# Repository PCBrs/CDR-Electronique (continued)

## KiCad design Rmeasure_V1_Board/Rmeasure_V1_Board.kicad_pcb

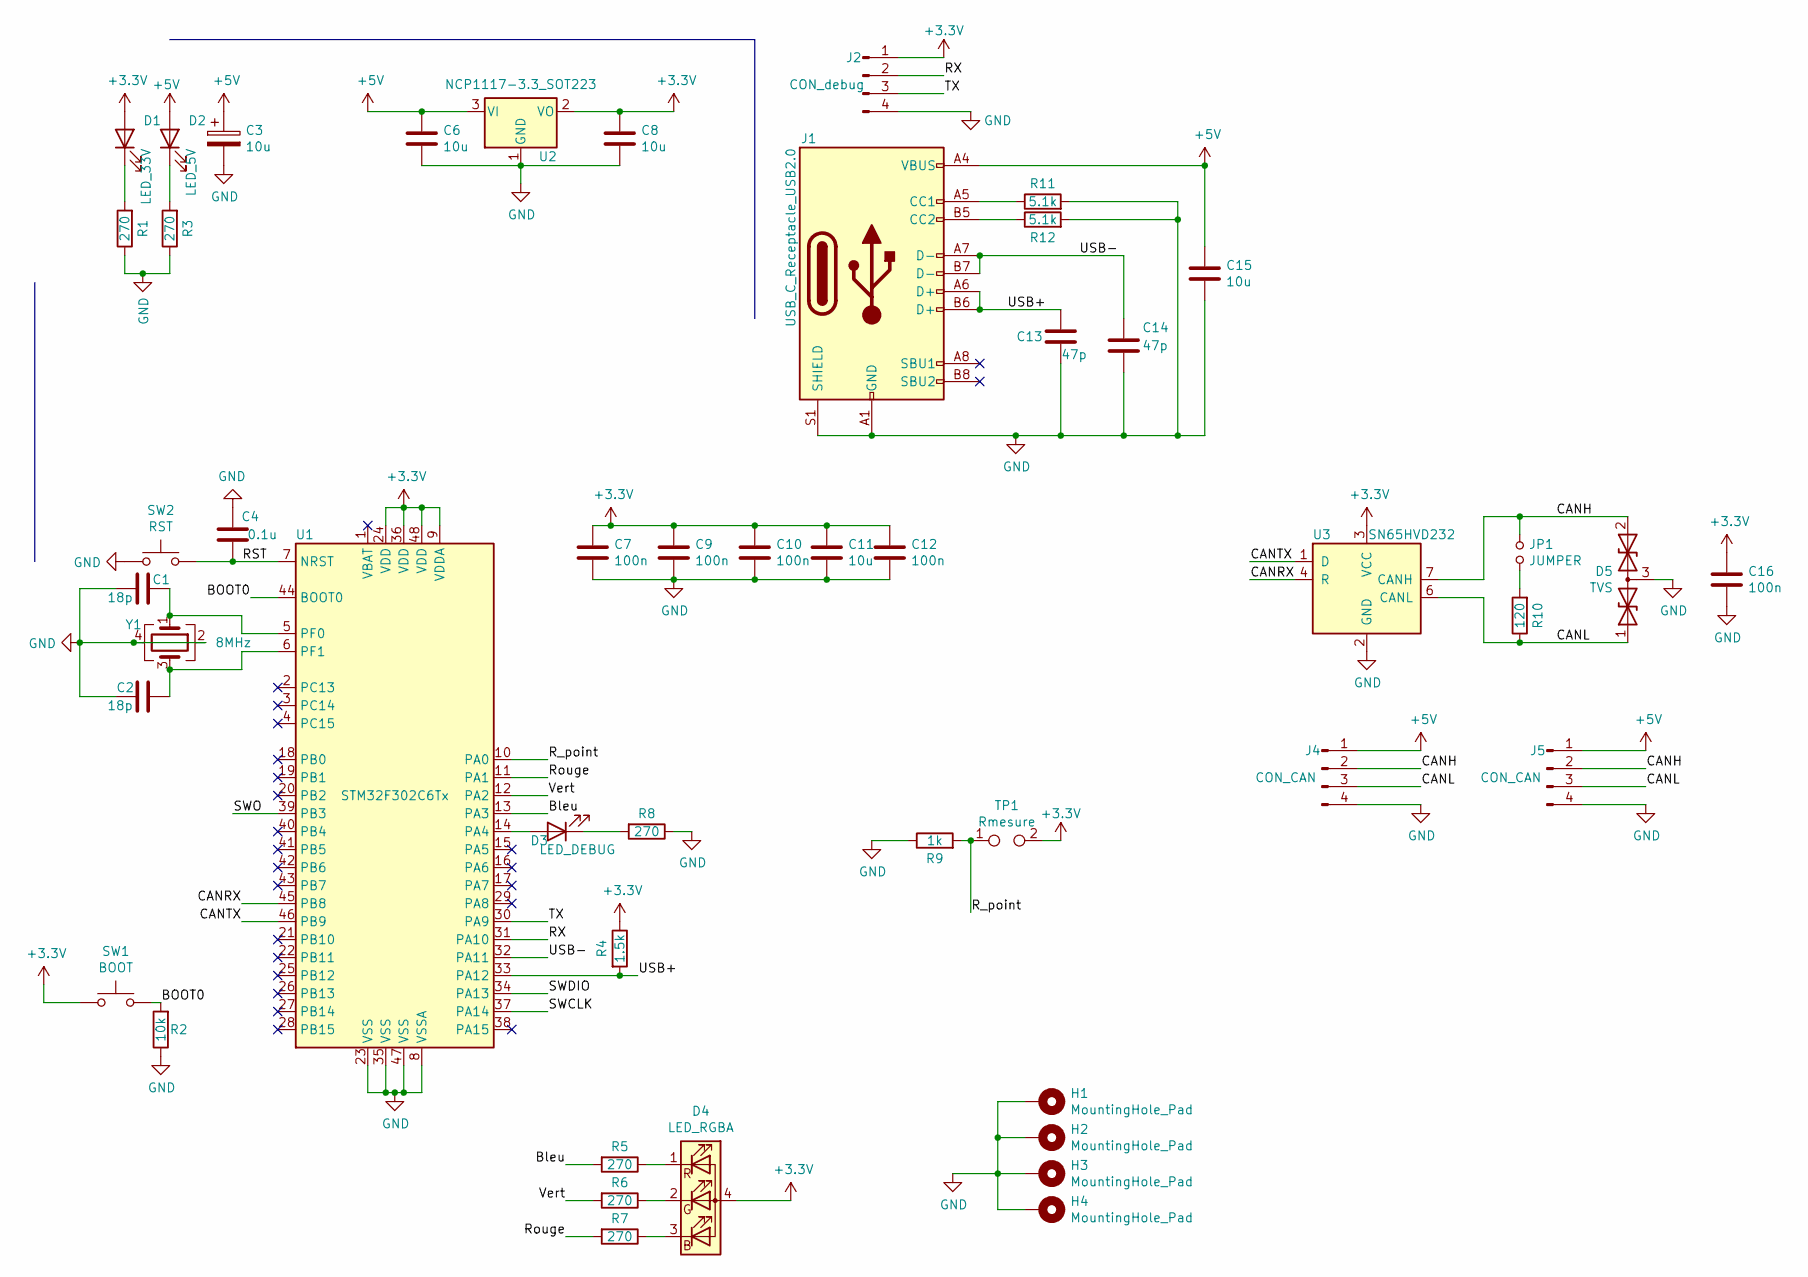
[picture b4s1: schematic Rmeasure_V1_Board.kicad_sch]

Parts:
C1, C2: 18p; C_0805_2012Metric_Pad1.18x1.45mm_HandSolder
C3: 10u; CP_Radial_D4.0mm_P2.00mm
C4: 0.1u; C_0805_2012Metric
C6, C8, C11, C15: 10u; C_0805_2012Metric
C7, C9, C10, C12, C16: 100n; C_0805_2012Metric
C13, C14: 47p; C_0805_2012Metric
D1: LED_33V; LED_0805_2012Metric
D2: LED_5V; LED_0805_2012Metric
D3: LED_DEBUG; LED_0805_2012Metric
D4: LED_RGBA; LED_SK6812_EC15_1.5x1.5mm
D5: TVS; SOT-23
H1, H2, H3, H4: MountingHole_Pad; MountingHole_3.2mm_M3_Pad_Via
J1: USB_C_Receptacle_USB2.0; USB_C_Receptacle_GCT_USB4085
J2: CON_debug; Wuerth_2.54mm_4pins_61900411121
J4, J5: CON_CAN; 690367290476
JP1: JUMPER; PinHeader_1x02_P2.54mm_Vertical
R1, R3, R5, R6, R7, R8: 270; R_0805_2012Metric
R2: 10k; R_0805_2012Metric
R4: 1.5k; R_0805_2012Metric
R9: 1k; R_0805_2012Metric
R10: 120; R_0805_2012Metric
R11, R12: 5.1k; R_0805_2012Metric
SW1: BOOT; SW_SPST_CK_RS282G05A3
SW2: RST; SW_SPST_CK_RS282G05A3
TP1: Rmesure; TestPoint_Pad_4.0x4.0mm
U1: STM32F302C6Tx; LQFP-48_7x7mm_P0.5mm
U2: NCP1117-3.3_SOT223; SOT-223-3_TabPin2
U3: SN65HVD232; SOIC-8_3.9x4.9mm_P1.27mm
Y1: 8MHz; Crystal_SMD_5032-4Pin_5.0x3.2mm

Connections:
+3V3: C7.1, C8.1, C9.1, C10.1, C11.1, C12.1, C16.1, D1.2 (A), D4.4 (A), J2.1, R4.1, SW1.1, TP1.2, U1.9 (VDDA), U1.24 (VDD), U1.36 (VDD), U1.48 (VDD), U2.2 (VO), U3.3 (VCC); also elsewhere on the board
+5V: C3.1, C6.1, C15.1, D2.2 (A), J1.A4 (VBUS), J1.A9 (VBUS), J1.B4 (VBUS), J1.B9 (VBUS), J4.1, J5.1, U2.3 (VI)
/BOOT0: R2.2, SW1.2, U1.44 (BOOT0); also elsewhere on the board
/Bleu: R5.2, U1.13 (PA3)
/CANH: D5.2 (A2), J4.2, J5.2, JP1.1, U3.7 (CANH)
/CANL: D5.1 (A1), J4.3, J5.3, R10.1, U3.6 (CANL)
/CANRX: U1.45 (PB8), U3.4 (R)
/CANTX: U1.46 (PB9), U3.1 (D)
/RST: C4.1, SW2.2, U1.7 (NRST); also elsewhere on the board
/RX: J2.2, U1.31 (PA10)
/R_point: R9.2, TP1.1, U1.10 (PA0)
/Rouge: R7.2, U1.11 (PA1)
/SWCLK: U1.37 (PA14)
/SWDIO: U1.34 (PA13)
/SWO: U1.39 (PB3)
/TX: J2.3, U1.30 (PA9)
/USB+: C13.1, J1.A6 (D+), J1.B6 (D+), R4.2, U1.33 (PA12)
/USB-: C14.1, J1.A7 (D-), J1.B7 (D-), U1.32 (PA11)
/Vert: R6.2, U1.12 (PA2)
GND: C1.2, C2.2, C3.2, C4.2, C6.2, C7.2, C8.2, C9.2, C10.2, C11.2, C12.2, C13.2, C14.2, C15.2, C16.2, D5.3 (common), H1.1, H2.1, H3.1, H4.1, J1.A1 (GND), J1.A12 (GND), J1.B1 (GND), J1.B12 (GND), J1.S1 (SHIELD), J2.4, J4.4, J5.4, R1.1, R2.1, R3.1, R8.1, R9.1, R11.2, R12.2, SW2.1, U1.8 (VSSA), U1.23 (VSS), U1.35 (VSS), U1.47 (VSS), U2.1 (GND), U3.2 (GND), Y1.2, Y1.4; also elsewhere on the board
unnamed: C1.1, U1.5 (PF0), Y1.1
unnamed: C2.1, U1.6 (PF1), Y1.3
unnamed: D1.1 (K), R1.2
unnamed: D2.1 (K), R3.2
unnamed: D3.1 (K), R8.2
unnamed: D3.2 (A), U1.14 (PA4)
unnamed: D4.1 (RK), R5.1
unnamed: D4.2 (GK), R6.1
unnamed: D4.3 (BK), R7.1
unnamed: J1.A5 (CC1), R11.1
unnamed: J1.B5 (CC2), R12.1
unnamed: JP1.2, R10.2

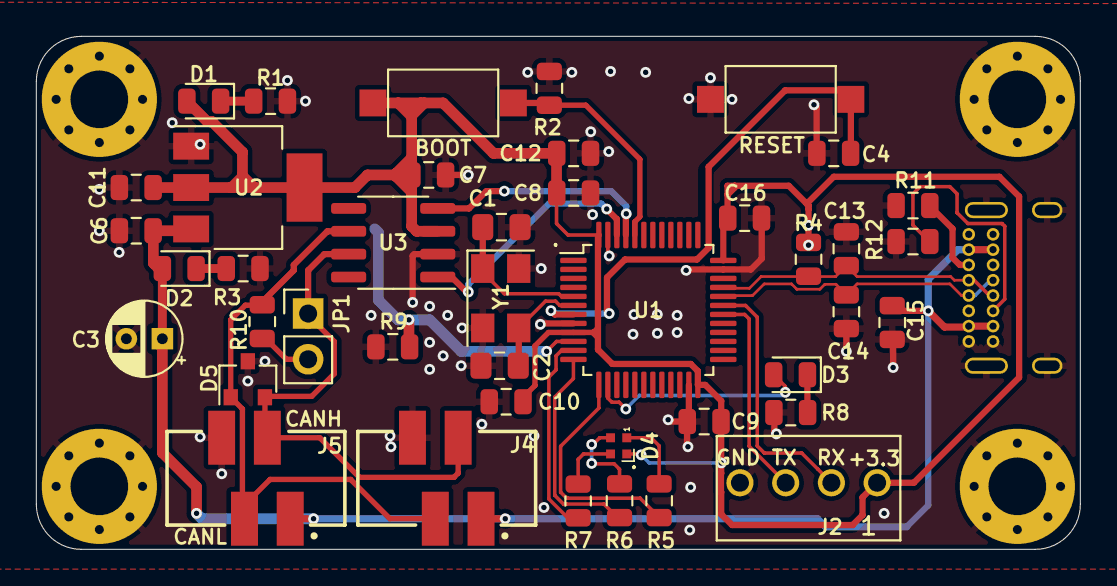
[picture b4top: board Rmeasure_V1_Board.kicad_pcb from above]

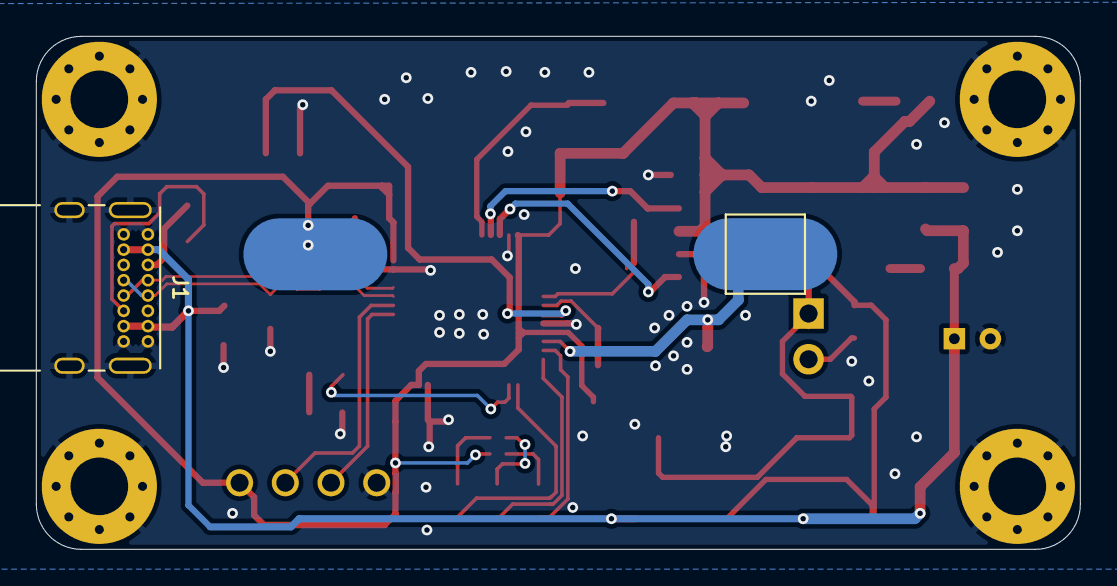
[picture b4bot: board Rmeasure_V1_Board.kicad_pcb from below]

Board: 2 copper layers, 58.0 x 28.5 mm, 48 parts (2 on the bottom side), 29 nets.

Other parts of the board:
BOOT: BOOT; SW_SPST_CK_RS282G05A3
RESET: RST; SW_SPST_CK_RS282G05A3

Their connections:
+3V3: BOOT.1; also elsewhere on the board
/BOOT0: BOOT.2; also elsewhere on the board
/RST: RESET.2; also elsewhere on the board
GND: RESET.1; also elsewhere on the board

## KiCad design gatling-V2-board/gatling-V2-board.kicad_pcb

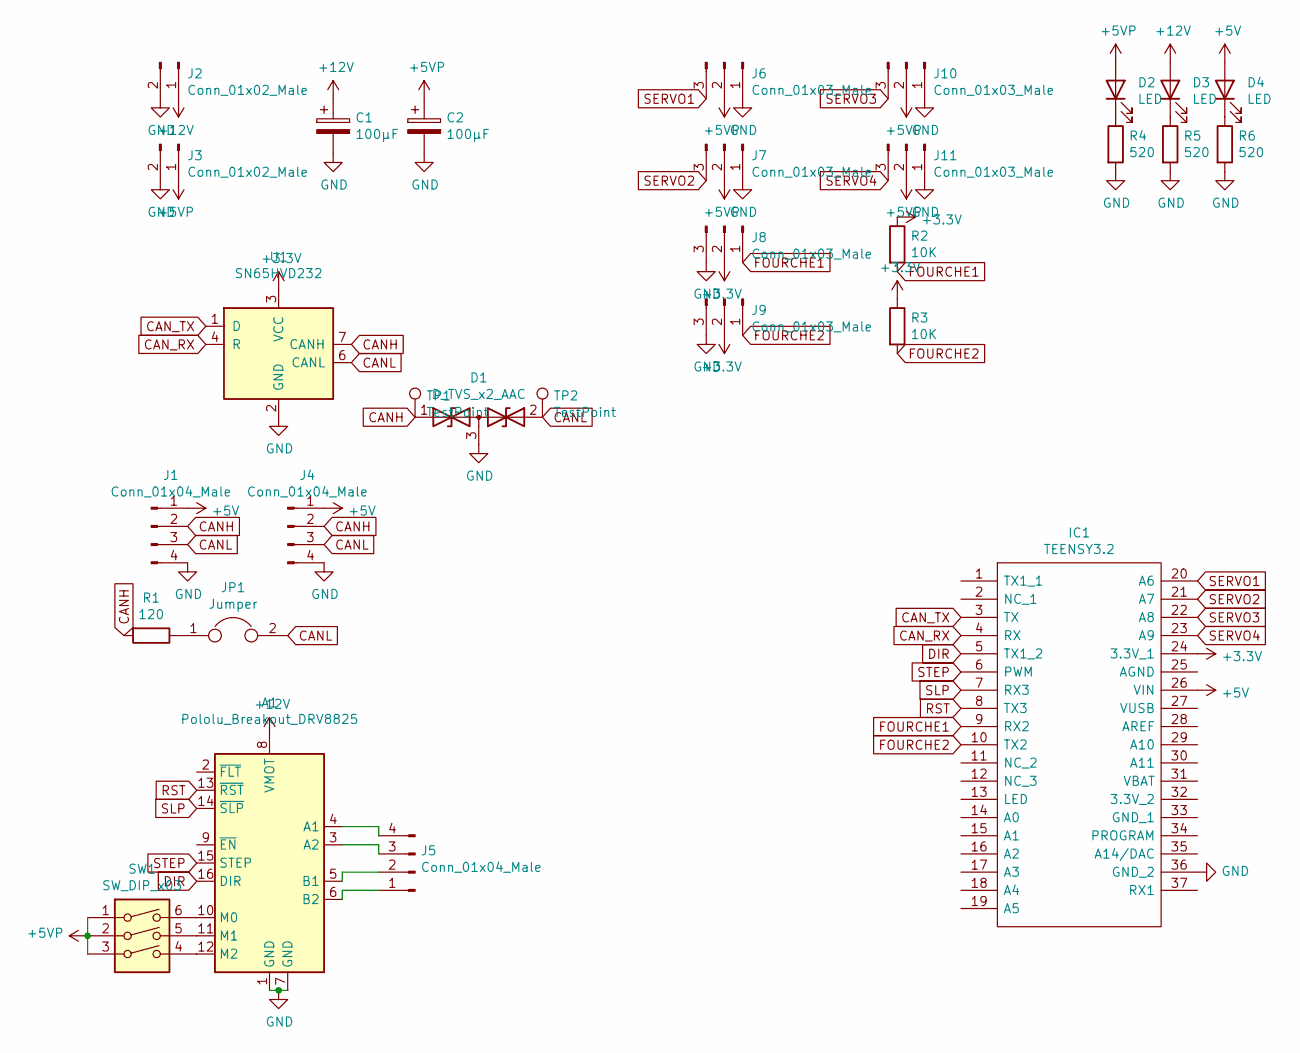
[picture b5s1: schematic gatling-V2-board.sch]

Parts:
A1: Pololu_Breakout_DRV8825; Pololu_Breakout-16_15.2x20.3mm
C1, C2: 100µF; CP_Radial_D8.0mm_P3.50mm
D1: D_TVS_x2_AAC; SOT-23
D2, D3, D4: LED; LED_0805_2012Metric
IC1: TEENSY3.2; TEENSY32; Manufacturer_Part_Number TEENSY3.2
J1, J4: Conn_01x04_Male; Wuerth_2mm_4pin_62000411622
J2, J3: Conn_01x02_Male; Wuerth_3.96mm_2pin_645002114822
J5: Conn_01x04_Male; PinHeader_1x04_P2.54mm_Horizontal
J6, J7, J8, J9, J10, J11: Conn_01x03_Male; Wuerth_2.54mm_3pins_61900311121
JP1: Jumper; PinHeader_1x02_P2.54mm_Vertical
R1: 120; R_0603_1608Metric
R2, R3: 10K; R_0603_1608Metric
R4, R5, R6: 520; R_0603_1608Metric
SW1: SW_DIP_x03; SW_DIP_SPSTx03_Slide_6.7x9.18mm_W6.73mm_P2.54mm_LowProfile_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
TP1, TP2: TestPoint; TestPoint_Keystone_5000-5004_Miniature
U1: SN65HVD232; SOIC-8_3.9x4.9mm_P1.27mm

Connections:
+3V3: IC1.24 (3.3V_1), J8.2, J9.2, R2.1, R3.1, U1.3 (VCC)
+5V: D4.2 (A), IC1.26 (VIN), J1.1, J4.1
+5VP: C2.1, D2.2 (A), J3.1, J6.2, J7.2, J10.2, J11.2, SW1.1, SW1.2, SW1.3
+12V: A1.8 (VMOT), C1.1, D3.2 (A), J2.1
CANH: D1.1 (A1), J1.2, J4.2, R1.2, TP1.1, U1.7 (CANH)
CANL: D1.2 (A2), J1.3, J4.3, JP1.2, TP2.1, U1.6 (CANL)
CAN_RX: IC1.4 (RX), U1.4 (R)
CAN_TX: IC1.3 (TX), U1.1 (D)
DIR: A1.16 (DIR), IC1.5 (TX1_2)
FOURCHE1: IC1.9 (RX2), J8.1, R2.2
FOURCHE2: IC1.10 (TX2), J9.1, R3.2
GND: A1.1 (GND), A1.7 (GND), C1.2, C2.2, D1.3 (common), IC1.36 (GND_2), J1.4, J2.2, J3.2, J4.4, J6.1, J7.1, J8.3, J9.3, J10.1, J11.1, R4.2, R5.2, R6.2, U1.2 (GND)
unnamed: A1.3 (A2), J5.3
unnamed: A1.4 (A1), J5.4
unnamed: A1.5 (B1), J5.2
unnamed: A1.6 (B2), J5.1
unnamed: A1.10 (M0), SW1.6
unnamed: A1.11 (M1), SW1.5
unnamed: A1.12 (M2), SW1.4
unnamed: D2.1 (K), R4.1
unnamed: D3.1 (K), R5.1
unnamed: D4.1 (K), R6.1
unnamed: JP1.1, R1.1
RST: A1.13 (~RST), IC1.8 (TX3)
SERVO1: IC1.20 (A6), J6.3
SERVO2: IC1.21 (A7), J7.3
SERVO3: IC1.22 (A8), J10.3
SERVO4: IC1.23 (A9), J11.3
SLP: A1.14 (~SLP), IC1.7 (RX3)
STEP: A1.15 (STEP), IC1.6 (PWM)

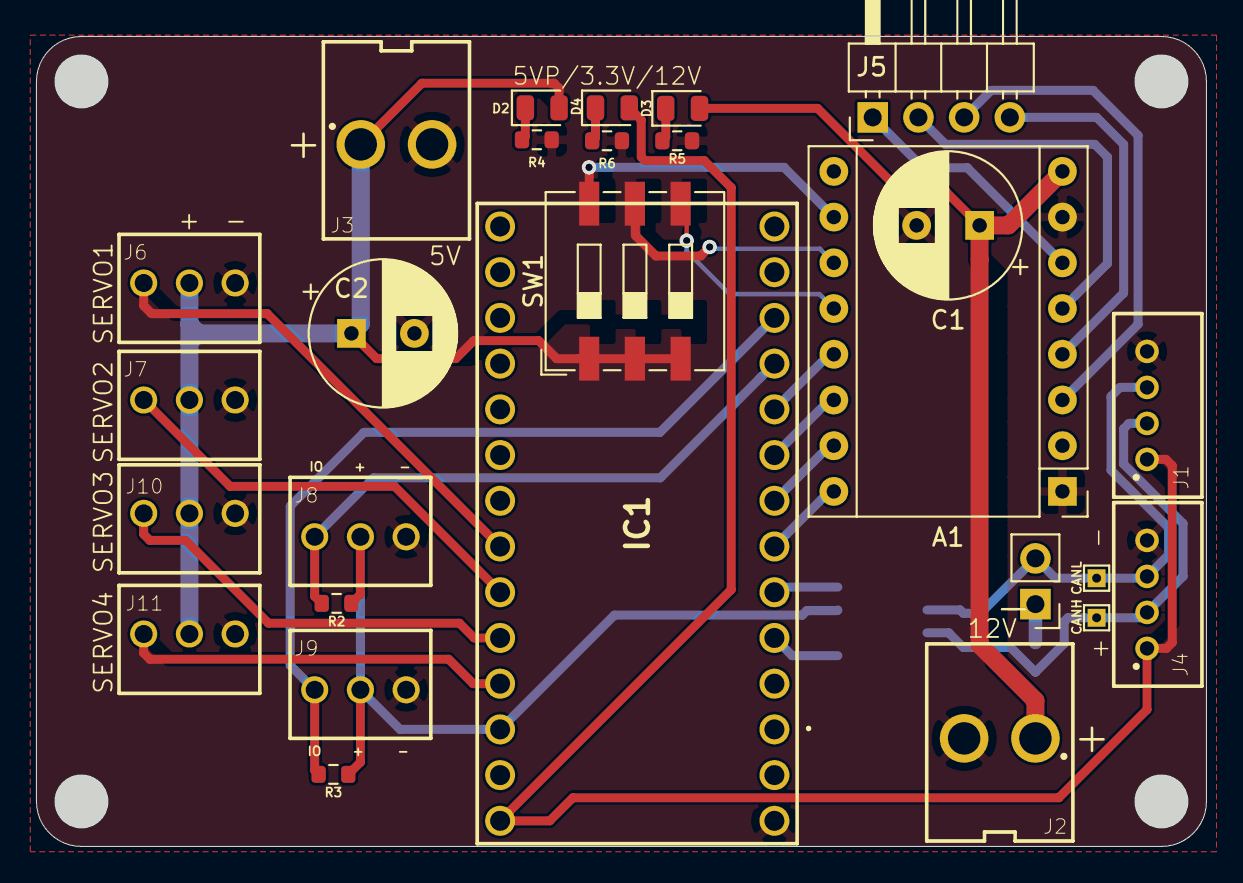
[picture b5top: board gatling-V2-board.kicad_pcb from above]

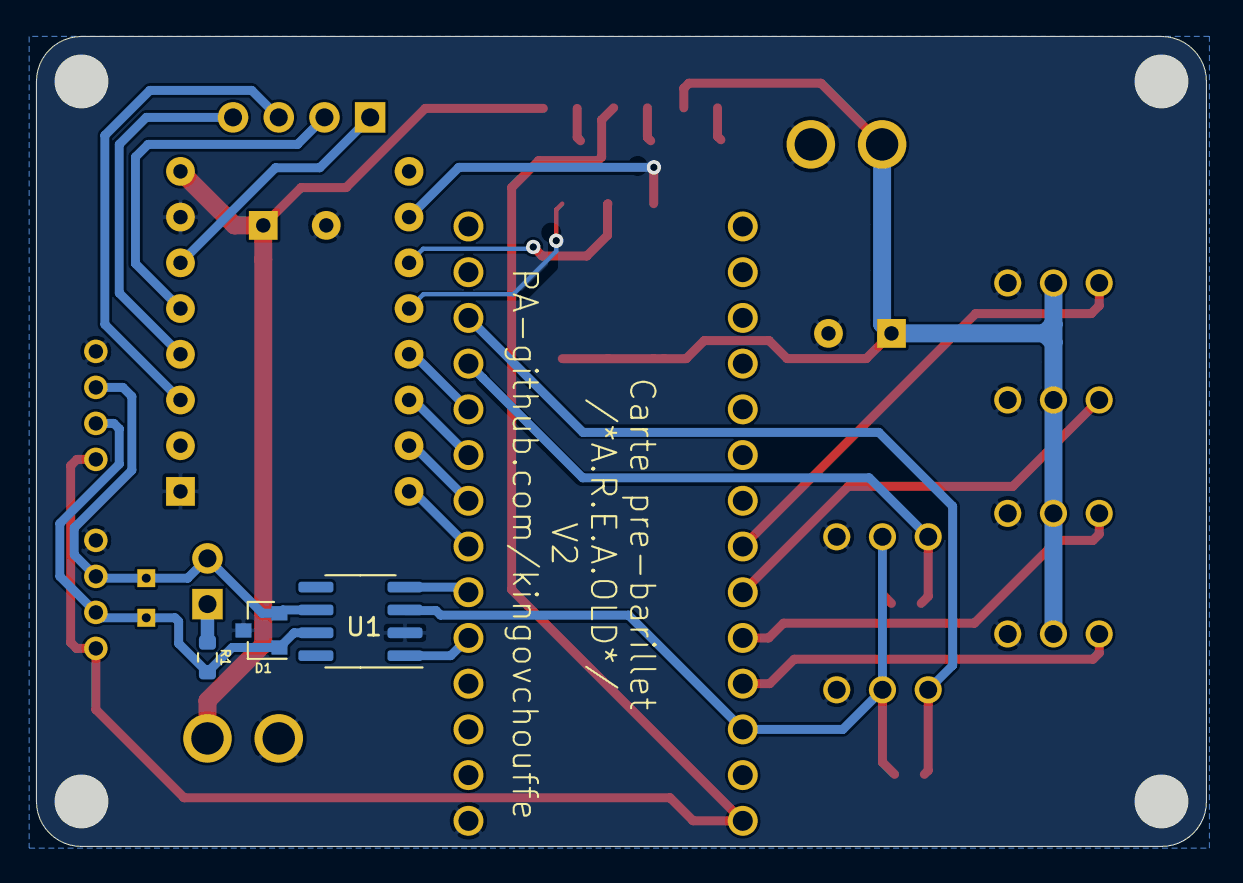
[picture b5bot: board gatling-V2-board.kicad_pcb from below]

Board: 2 copper layers, 65.0 x 45.0 mm, 30 parts (3 on the bottom side), 30 nets.

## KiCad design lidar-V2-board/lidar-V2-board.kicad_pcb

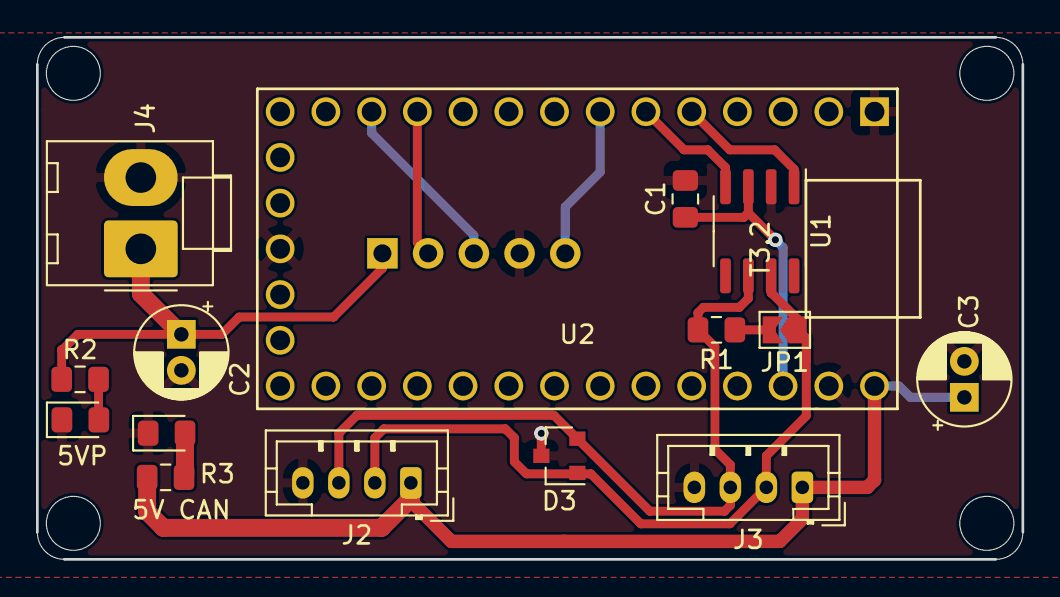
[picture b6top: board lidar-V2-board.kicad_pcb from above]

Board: 2 copper layers, 54.8 x 29.0 mm, 16 parts (1 on the bottom side), 14 nets.

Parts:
C1: 100nF; C_0805_2012Metric_Pad1.15x1.40mm_HandSolder
C2: 100µF; CP_Radial_D5.0mm_P2.00mm
C3: 20µF; CP_Radial_D5.0mm_P2.00mm
D1, D2: LED; LED_0805_2012Metric_Pad1.15x1.40mm_HandSolder
D3: SM712_SOT23; SOT-23
J1: Conn_01x05_Female; PinHeader_1x05_P2.54mm_Vertical
J2, J3: Conn_01x04_Male; JST_PH_B4B-PH-K_1x04_P2.00mm_Vertical
J4: Conn_01x02_Male; Molex_KK-396_A-41791-0002_1x02_P3.96mm_Vertical
JP1: SolderJumper_2_Open; SolderJumper-2_P1.3mm_Open_TrianglePad1.0x1.5mm
R1: 120; R_0805_2012Metric_Pad1.15x1.40mm_HandSolder
R2, R3: 220; R_0805_2012Metric_Pad1.15x1.40mm_HandSolder
U1: SN65HVD232; SOIC-8_3.9x4.9mm_P1.27mm
U2: Teensy3.2; Teensy30_31_32_LC

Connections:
3.3V: C1.1, U1.3, U2.31
+5C: C3.1, J2.1, J3.1, R3.1, U2.33
+5P: C2.1, J1.1, J4.1, R2.1
CANH: D3.1, J2.2, J3.2, JP1.1, U1.7
CANL: D3.2, J2.3, J3.3, R1.2, U1.6
CANRX: U1.4, U2.6
CANTX: U1.1, U2.5
GND: C1.2, C2.2, C3.2, D1.1, D2.1, D3.3, J1.4, J2.4, J3.4, J4.2, U1.2, U2.1, U2.17, U2.32
LRX: J1.3, U2.12
LTX: J1.2, U2.11
MOTPWM: J1.5, U2.7
unnamed: D1.2, R2.2
unnamed: D2.2, R3.2
unnamed: JP1.2, R1.1

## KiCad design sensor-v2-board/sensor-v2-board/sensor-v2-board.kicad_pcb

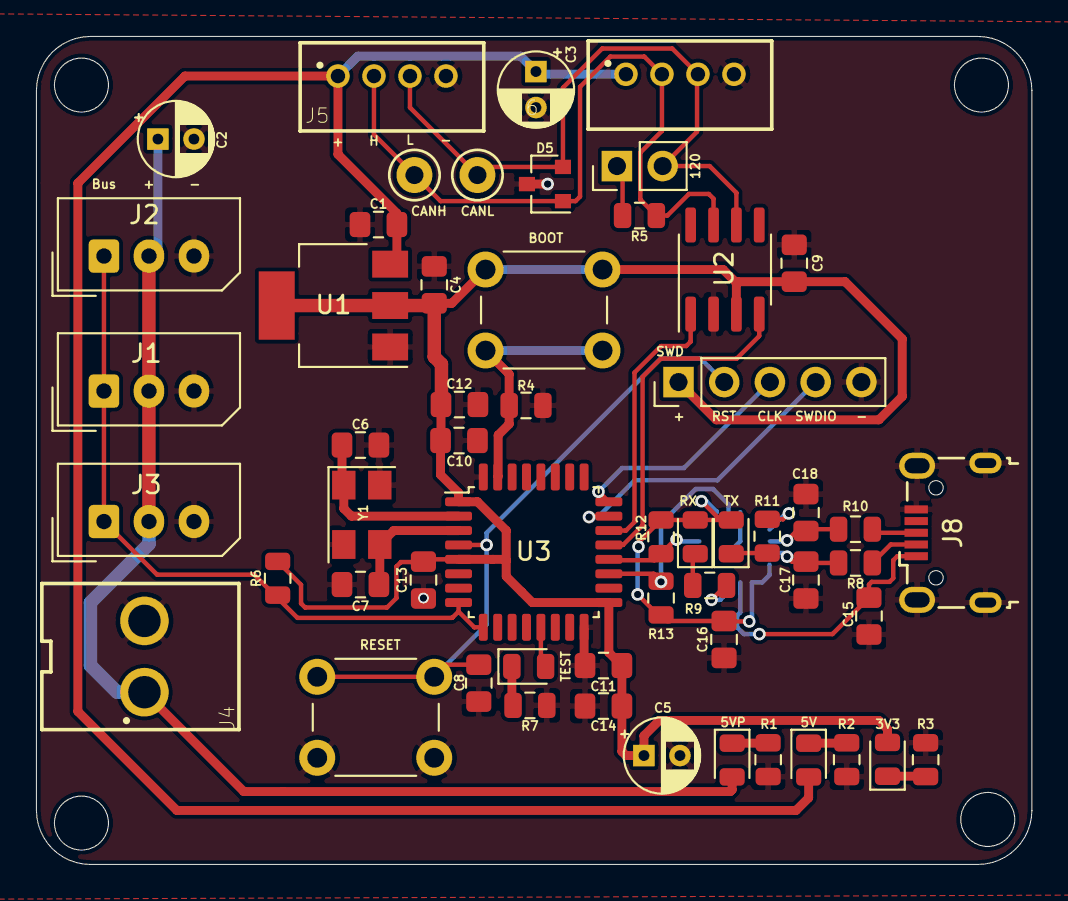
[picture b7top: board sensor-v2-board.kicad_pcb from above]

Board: 2 copper layers, 55.3 x 46.0 mm, 56 parts (1 on the bottom side), 33 nets.

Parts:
3V3, 5V, 5VP: 5vpLED; LED_0805_2012Metric
120: Jumper_2_Open; PinHeader_1x02_P2.54mm_Vertical
BOOT: Boot_Switch; SW_PUSH_6mm
C1, C4: 10µF; C_0805_2012Metric_Pad1.15x1.40mm_HandSolder
C2, C3, C5: 10µF; CP_Radial_D4.0mm_P2.00mm
C6, C7: 18pF; C_0805_2012Metric_Pad1.15x1.40mm_HandSolder
C8: 0.1µF; C_0805_2012Metric_Pad1.15x1.40mm_HandSolder
C9, C12, C13, C16: 100nF; C_0805_2012Metric_Pad1.15x1.40mm_HandSolder
C10, C11: 4.7µF; C_0805_2012Metric_Pad1.15x1.40mm_HandSolder
C14: 1µF; C_0805_2012Metric_Pad1.15x1.40mm_HandSolder
C15: 10nF; C_0805_2012Metric_Pad1.15x1.40mm_HandSolder
C17, C18: 47pF; C_0805_2012Metric_Pad1.15x1.40mm_HandSolder
CANH: TestPoint; TestPoint_Keystone_5000-5004_Miniature
CANL: TestPoint; TestPoint_Keystone_5000-5004_Miniature
D5: D_TVS_x2_AAC; SOT-23
J1, J2, J3: Conn_01x03_Male; Molex_SPOX_5267-03A_1x03_P2.50mm_Vertical
J4: Conn_01x02_Male; Wuerth_3.96mm_2pin_645002114822
J5, J6: Conn_01x04_Male; Wuerth_2mm_4pin_62000411622
J8: USB_B_Micro; USB_Micro-B_Wuerth_629105150521
R1, R2, R3, R7, R8, R9, R10, R11: 270; R_0805_2012Metric
R4, R12, R13: 10k; R_0805_2012Metric
R5: 120; R_0805_2012Metric
R6: 1.5k; R_0805_2012Metric
RESET: RST_Push; SW_PUSH_6mm
RX: RX_LED; LED_0805_2012Metric
SWD: Conn_01x05_Male; PinHeader_1x05_P2.54mm_Vertical
TEST: TST_LED; LED_0805_2012Metric
TX: TX_LED; LED_0805_2012Metric
U1: NCP1117-3.3_SOT223; SOT-223-3_TabPin2
U2: SN65HVD232; SOIC-8_3.9x4.9mm_P1.27mm
U3: STM32F042K6Tx; LQFP-32_7x7mm_P0.8mm
Ue: FT230XQ; QFN-16-1EP_4x4mm_P0.65mm_EP2.1x2.1mm
Y1: 8MHz; Crystal_SMD_5032-4Pin_5.0x3.2mm

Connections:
5VUSB: C15.1, J8.1, Ue.10
+3V3: 3V3.2, BOOT.1, C4.1, C5.1, C9.1, C10.1, C11.1, C12.1, C13.1, C14.1, R6.2, SWD.1, U1.2, U2.3, U3.1, U3.5, U3.17
+5V: 5V.2, C1.1, C3.1, J5.1, J6.1, U1.3
+5VP: 5VP.2, C2.1, J1.2, J2.2, J3.2, J4.1
CANH: CANH.1, D5.1, J5.2, J6.2, R5.1, U2.7
CANL: 120.2, CANL.1, D5.2, J5.3, J6.3, U2.6
CAN_RX: U2.4, U3.21
CAN_TX: U2.1, U3.22
GND: C1.2, C2.2, C3.2, C4.2, C5.2, C6.2, C7.2, C8.1, C9.2, C10.2, C11.2, C12.2, C13.2, C14.2, C15.2, C16.2, C17.2, C18.2, D5.3, J1.3, J2.3, J3.3, J4.2, J5.4, J6.4, J8.5, J8.6, R1.1, R2.1, R3.1, R4.1, R7.2, RESET.2, SWD.5, U1.1, U2.2, U3.16, U3.32, Ue.3, Ue.13, Ue.17, Y1.2, Y1.4
unnamed: C6.1, U3.2, Y1.1
unnamed: C7.1, U3.3, Y1.3
unnamed: C16.1, R12.2, R13.2, RX.2, TX.2, Ue.1, Ue.8, Ue.9
unnamed: 5VP.1, R1.2
unnamed: 5V.1, R2.2
unnamed: 3V3.1, R3.2
unnamed: R7.1, TEST.1
unnamed: TEST.2, U3.13
unnamed: R9.2, RX.1
unnamed: R11.1, TX.1
unnamed: 120.1, R5.2
unnamed: BOOT.2, R4.2, U3.31
unnamed: R9.1, Ue.11
unnamed: R11.2, Ue.5
RST: C8.2, RESET.1, SWD.2, U3.4
RXD: R13.1, U3.19, Ue.2
SERVO_BUS: J1.1, J2.1, J3.1, R6.1, U3.8, U3.9
SWDCLK: SWD.3, U3.24
SWDIO: SWD.4, U3.23
TXD: R12.1, U3.20, Ue.15
USB_DM: J8.2, R8.2
USB_DMo: C17.1, R8.1, Ue.7
USB_DP: J8.3, R10.2
USB_DPO: C18.1, R10.1, Ue.6
